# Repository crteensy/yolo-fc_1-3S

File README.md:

# Yolo FC, STM32F7, 1-3S
This FC has been test flown with a 3" toothpick, and it flew well.

- Main MCU: STM32F745
- IMU: ICM-20602
- Flash: 8MB
- Baro: BMP280
- OSD: '7456
- GNSS: Integrated GPS module (uBlox ZOE-M8Q) with u.Fl connector and experimental support for active antennas
- 4 ESCs:
  - EFM8BB21 / bluejay
  - Calculated current rating of 20A continuous 30A burst (depending on the airflow cooling situation)
- Current sensor: INA186 with 0m5 shunt - subjectively some of the best current measurements we have seen on any FC
- 4 multi purpose expansion connectors:
  - each with its own UART
  - shared I2C bus
  - 5V, 3V3 and GND
  - a multi-purpose pin for analog RSSI, Buzzer, LEDs, etc.
- One video expansion connector:
  - Camera in and VTx out
  - UART
  - 2 multi-purpose pins
  - switchable 5V (*)
- size: 30 x 25.2 mm

The expansion connectors can be used with very simple or more complex plug-ins for
- Rx of your choice
- Magnetometer
- Buzzer
- LED strip
- dual camera switching on the OSD connector
- even additional plugin ESCs for hexa- and octocopters are possible

*) The OSD connector has a 5V output that is only ON when USB is not plugged in. This protects your USB port from power hungry VTx'es that might overload the port. However, that feature can be disabled with a solder bridge.

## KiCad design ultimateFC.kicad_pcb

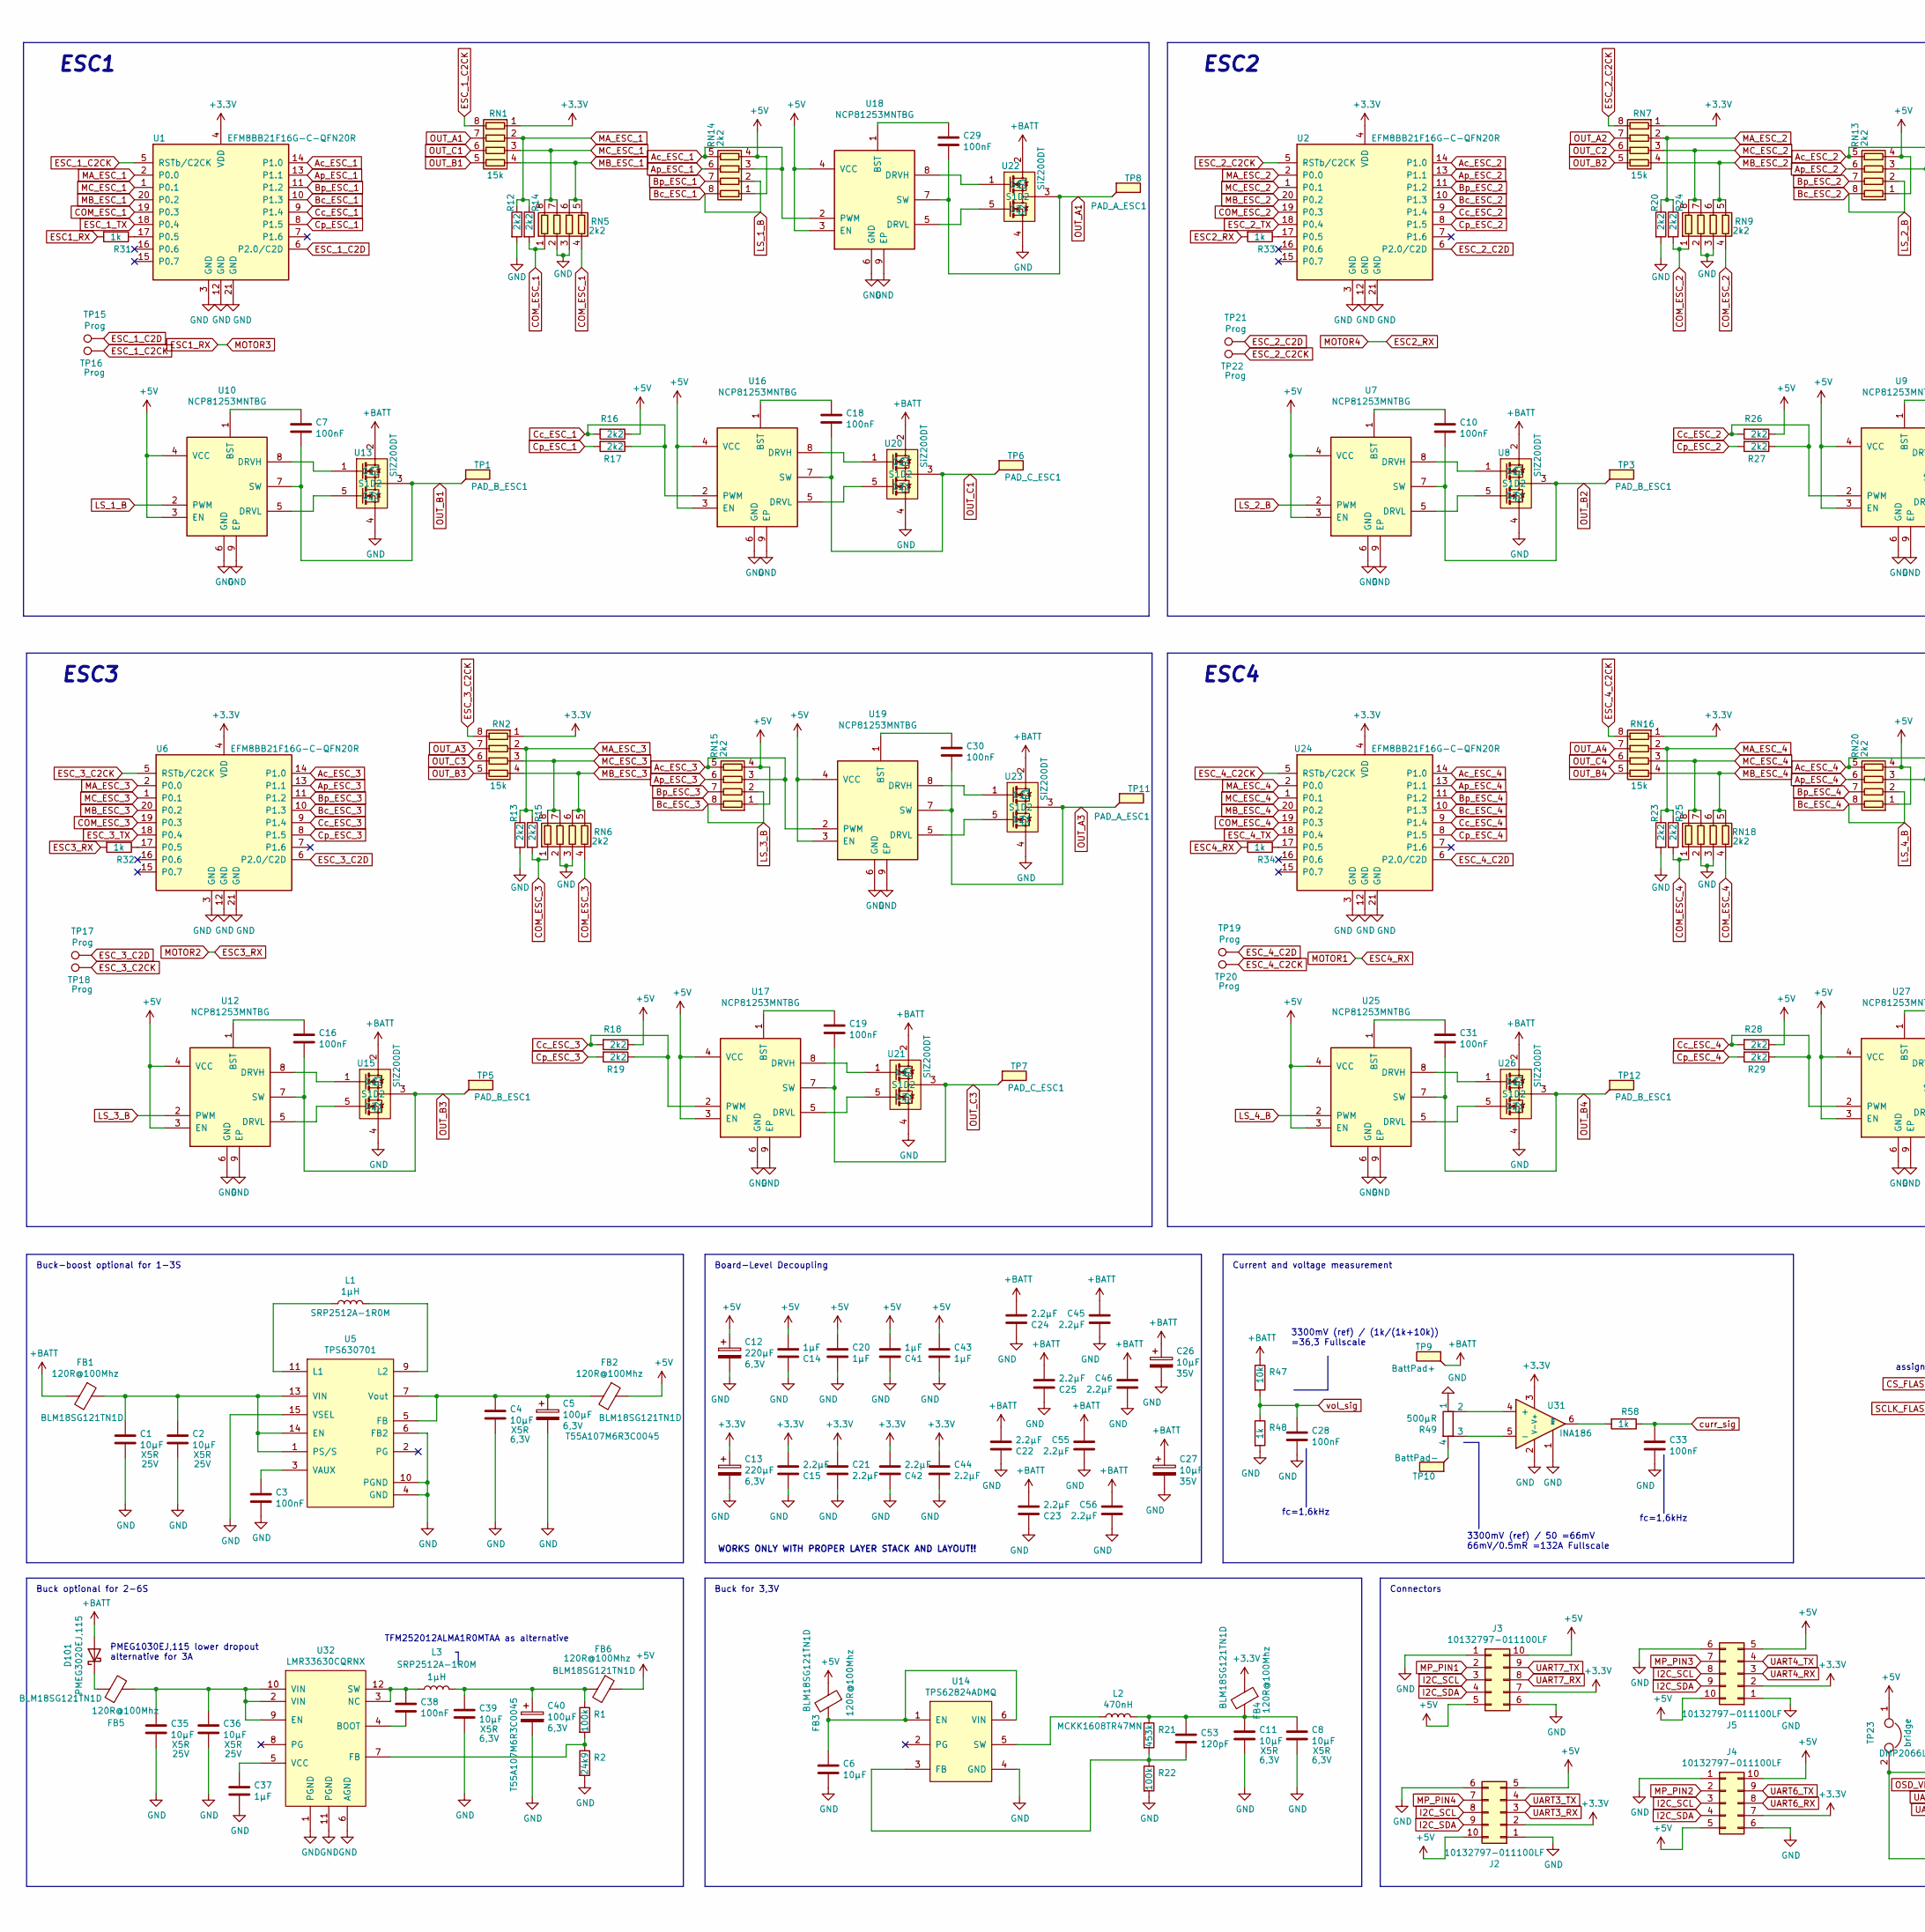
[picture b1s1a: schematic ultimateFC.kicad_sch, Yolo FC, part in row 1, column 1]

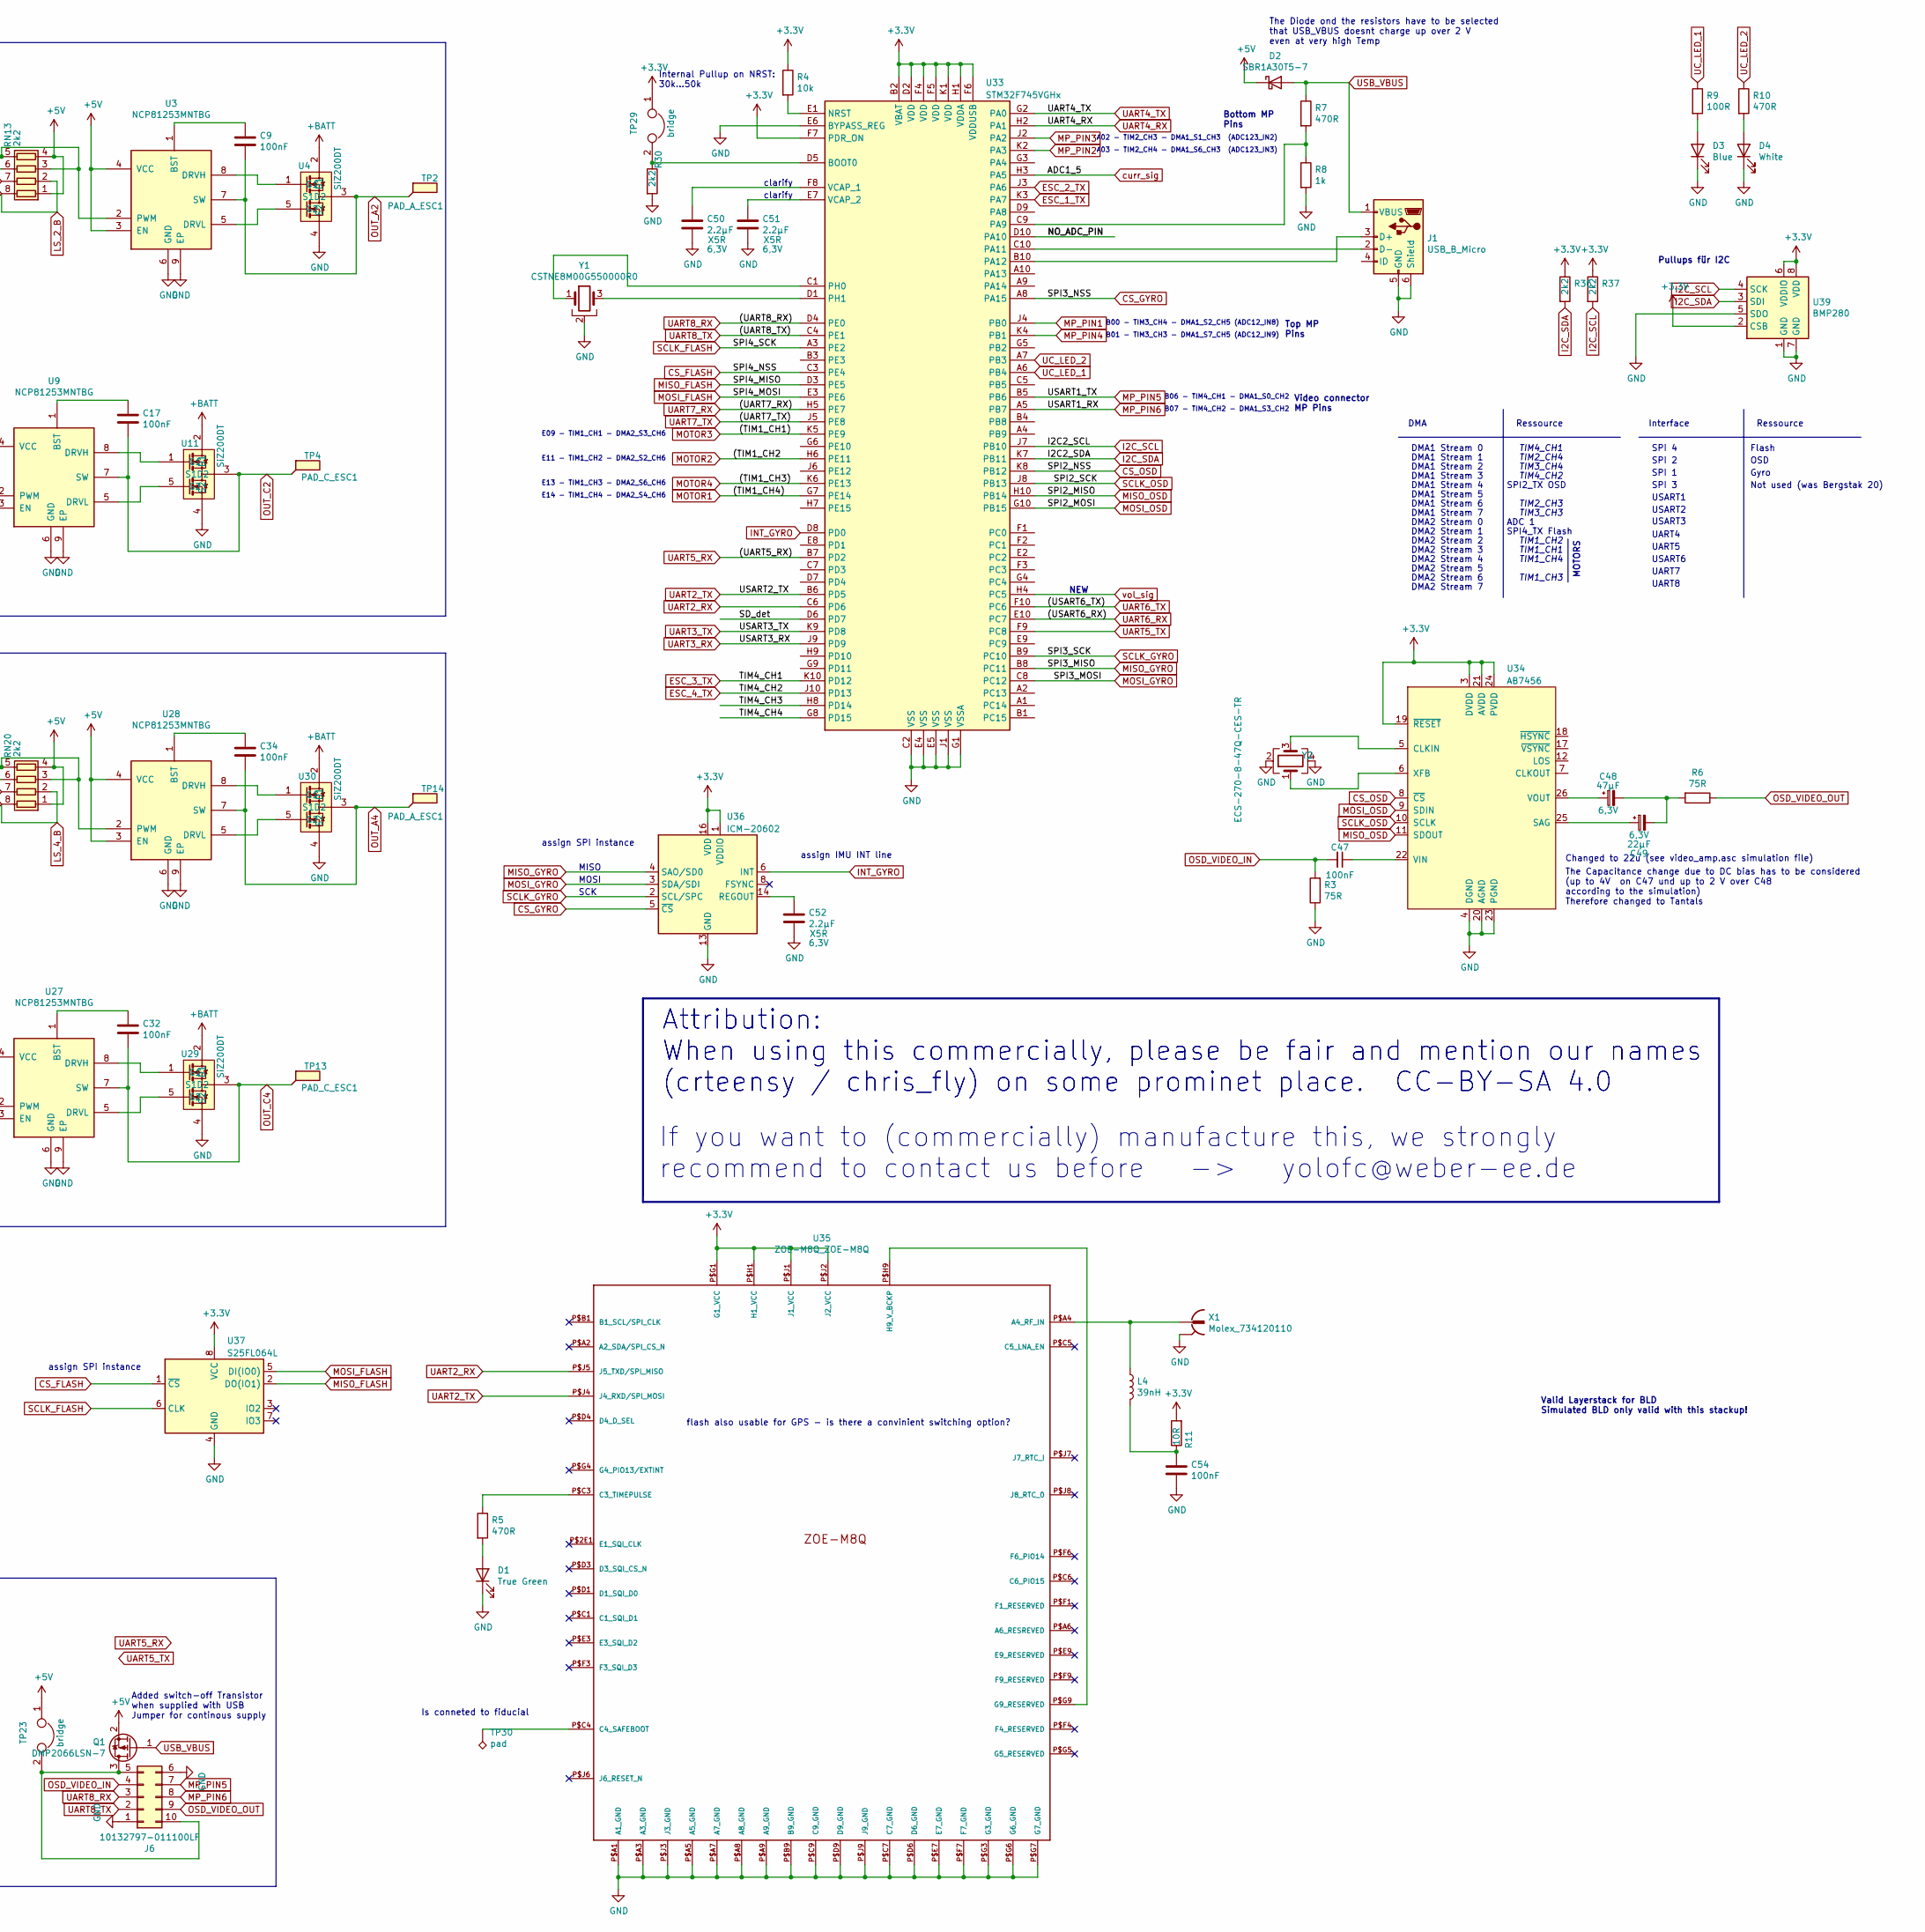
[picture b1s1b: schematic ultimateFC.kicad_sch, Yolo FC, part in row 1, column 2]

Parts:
C1, C2, C35, C36: 10µF; C_1206_3216Metric
C3, C28, C33, C38, C47, C54: 100nF; C_0201_0603Metric_mod
C4, C6, C8, C11, C39: 10µF; C_0603_1608Metric
C5, C40: 100µF; CP_EIA-3216-10_Kemet-I
C7, C9, C10, C16, C17, C18, C19, C29, C30, C31, C32, C34: 100nF; C_0402_1005Metric
C12, C13: 220µF; CP_EIA-3528-15_AVX-H
C14, C20, C41, C43: 1µF; C_AVX_Super_Low_ESL
C15, C21, C42, C44: 2.2µF; C_AVX_Super_Low_ESL
C22, C23, C24, C25, C45, C46, C55, C56: 2.2µF; C_0603_1608Metric
C26, C27: 10µF; CP_EIA-3216-18_Kemet-A
C37: 1µF; C_0402_1005Metric
C48: 47µF; C_0603_1608Metric
C49: 22µF; C_0603_1608Metric
C50, C51, C52: 2.2µF; C_0402_1005Metric
C53: 120pF; C_0201_0603Metric_mod
D1: True Green; LED_0201_0603Metric
D2: SBR1A30T5-7; D_SOD-523
D3: Blue; LED_0201_0603Metric
D4: White; LED_0201_0603Metric
D101: PMEG3020EJ,115; D_SOD-323
FB1, FB2, FB3, FB4, FB5, FB6: 120R@100Mhz; L_0603_1608Metric
J1: USB_B_Micro; USB_Micro-B_Molex_47346-0001
J2, J3, J4, J5, J6: 10132797-011100LF
L1, L3: 1µH; L_Wuerth_MAPI-2506
L2: 470nH; L_0603_1608Metric
L4: 39nH; L_0201_0603Metric
Q1: DMP2066LSN-7; SOT-323_SC-70
R1, R22: 100k; R_0201_0603Metric_mod
R2: 24k9; R_0201_0603Metric_mod
R3, R6: 75R; R_0402_1005Metric
R4: 10k; R_0201_0603Metric_mod
R5, R7, R10: 470R; R_0201_0603Metric_mod
R8, R31, R32, R33, R34, R48, R58: 1k; R_0201_0603Metric_mod
R9: 100R; R_0201_0603Metric_mod
R11: 10R; R_0201_0603Metric_mod
R12, R13, R14, R15, R16, R17, R18, R19, R20, R23, R24, R25, R26, R27, R28, R29, R30, R36, R37: 2k2; R_0201_0603Metric_mod
R21: 453k; R_0201_0603Metric_mod
R47: 10k; R_0402_1005Metric
R49: 500µR; R_Shunt_Vishay_WSKW0612
RN1, RN2, RN7, RN16: 15k; R_Array_Convex_4x0402
RN5, RN6, RN9, RN13, RN14, RN15, RN18, RN20: 2k2; EXB18V_0201x4
TP1, TP3, TP5, TP12: PAD_B_ESC1; esc_pad
TP2, TP8, TP11, TP14: PAD_A_ESC1; esc_pad
TP4, TP6, TP7, TP13: PAD_C_ESC1; esc_pad
TP9: BattPad+; batt_conn_oval
TP10: BattPad-; batt_conn_oval
TP15, TP16, TP17, TP18, TP19, TP20, TP21, TP22: Prog; programm_pad_esc
TP23, TP29: bridge; solderbridge_tiny
TP30: pad; TestPoint_Pad_1.0x1.0mm
U1, U2, U6, U24: EFM8BB21F16G-C-QFN20R; SiliconLabs_QFN-20-1EP_3x3mm_P0.5mm
U3, U7, U9, U10, U12, U16, U17, U18, U19, U25, U27, U28: NCP81253MNTBG; DFN-8-1EP_2x2mm_P0.5mm_EP0.9x1.3mm
U4, U8, U11, U13, U15, U20, U21, U22, U23, U26, U29, U30: SiZ200DT; PowerPAIR3.3x3.3
U5: TPS630701; TEXAS_15-VQFN-HR
U14: TPS62824ADMQ; VSON_HR6
U31: INA186; SOT-363_SC-70-6
U32: LMR33630CQRNX; Texas_RNX0012B
U33: STM32F745VGHx; TFBGA-100_8x8mm_Layout10x10_P0.8mm
U34: AB7456; TSSOP-28_4.4x9.7mm_P0.65mm
U35: ZOE-M8Q_ZOE-M8Q; ZOE-M8
U36: ICM-20602; LGA-16_3x3mm_P0.5mm_LayoutBorder3x5y
U37: S25FL064L; WSON-8_4x4mm_P0.8mm
U39: BMP280; Bosch_LGA-8_2x2.5mm_P0.65mm_ClockwisePinNumbering
X1: Molex_734120110
Y1: CSTNE8M00G550000R0; Resonator_SMD_muRata_CSTxExxV-3Pin_3.0x1.1mm
Y2: ECS-270-8-47Q-CES-TR; ECX-1247Q

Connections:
+3V3: C13.1, C15.2, C21.1, C42.2, C44.1, FB4.1, J2.2, J3.7, J4.7, J5.2, R4.1, R11.2, R36.1, R37.1, RN1.1 (R1.1), RN2.1 (R1.1), RN7.1 (R1.1), RN16.1 (R1.1), TP29.1, U1.4 (VDD), U2.4 (VDD), U6.4 (VDD), U24.4 (VDD), U31.3 (V+), U33.B2 (VBAT), U33.D2 (VDD), U33.F4 (VDD), U33.F5 (VDD), U33.F6 (VDDUSB), U33.F7 (PDR_ON), U33.H1 (VDDA), U33.K1 (VDD), U34.3 (DVDD), U34.19 (~RESET), U34.21 (AVDD), U34.24 (PVDD), U35.P$G1 (G1_VCC), U35.P$H1 (H1_VCC), U35.P$J1 (J1_VCC), U35.P$J2 (J2_VCC), U36.1 (VDDIO), U36.16 (VDD), U37.8 (VCC), U39.2 (CSB), U39.6 (VDDIO), U39.8 (VDD)
+5V: C12.1, C14.2, C20.1, C41.2, C43.1, D2.1 (K), FB2.1, FB3.1, FB6.1, J2.5, J2.10, J3.5, J3.10, J4.5, J4.10, J5.5, J5.10, Q1.2 (S), R16.1, R18.1, R26.1, R28.1, RN13.1 (R1.1), RN13.4 (R4.1), RN14.1 (R1.1), RN14.4 (R4.1), RN15.1 (R1.1), RN15.4 (R4.1), RN20.1 (R1.1), RN20.4 (R4.1), TP23.1, U3.3 (EN), U3.4 (VCC), U7.3 (EN), U7.4 (VCC), U9.3 (EN), U9.4 (VCC), U10.3 (EN), U10.4 (VCC), U12.3 (EN), U12.4 (VCC), U16.3 (EN), U16.4 (VCC), U17.3 (EN), U17.4 (VCC), U18.3 (EN), U18.4 (VCC), U19.3 (EN), U19.4 (VCC), U25.3 (EN), U25.4 (VCC), U27.3 (EN), U27.4 (VCC), U28.3 (EN), U28.4 (VCC)
+BATT: C22.2, C23.2, C24.2, C25.2, C26.1, C27.1, C45.1, C46.1, C55.1, C56.1, D101.2 (A), FB1.2, R47.1, TP9.1, U4.2 (D1), U8.2 (D1), U11.2 (D1), U13.2 (D1), U15.2 (D1), U20.2 (D1), U21.2 (D1), U22.2 (D1), U23.2 (D1), U26.2 (D1), U29.2 (D1), U30.2 (D1)
/NO_ADC_PIN: U33.D10 (PA10)
/SD_det: U33.D6 (PD7)
/TIM4_CH3: U33.H8 (PD14)
/TIM4_CH4: U33.G8 (PD15)
Ac_ESC_1: RN14.3 (R3.1), RN14.5 (R4.2), U1.14 (P1.0), U18.2 (PWM)
Ac_ESC_2: RN13.3 (R3.1), RN13.5 (R4.2), U2.14 (P1.0), U3.2 (PWM)
Ac_ESC_3: RN15.3 (R3.1), RN15.5 (R4.2), U6.14 (P1.0), U19.2 (PWM)
Ac_ESC_4: RN20.3 (R3.1), RN20.5 (R4.2), U24.14 (P1.0), U28.2 (PWM)
Ap_ESC_1: RN14.6 (R3.2), U1.13 (P1.1)
Ap_ESC_2: RN13.6 (R3.2), U2.13 (P1.1)
Ap_ESC_3: RN15.6 (R3.2), U6.13 (P1.1)
Ap_ESC_4: RN20.6 (R3.2), U24.13 (P1.1)
Bc_ESC_1: RN14.2 (R2.1), RN14.8 (R1.2), U1.10 (P1.3), U10.2 (PWM)
Bc_ESC_2: RN13.2 (R2.1), RN13.8 (R1.2), U2.10 (P1.3), U7.2 (PWM)
Bc_ESC_3: RN15.2 (R2.1), RN15.8 (R1.2), U6.10 (P1.3), U12.2 (PWM)
Bc_ESC_4: RN20.2 (R2.1), RN20.8 (R1.2), U24.10 (P1.3), U25.2 (PWM)
Bp_ESC_1: RN14.7 (R2.2), U1.11 (P1.2)
Bp_ESC_2: RN13.7 (R2.2), U2.11 (P1.2)
Bp_ESC_3: RN15.7 (R2.2), U6.11 (P1.2)
Bp_ESC_4: RN20.7 (R2.2), U24.11 (P1.2)
COM_ESC_1: R14.2, RN5.1 (R1.1), RN5.4 (R4.1), U1.19 (P0.3)
COM_ESC_2: R24.2, RN9.1 (R1.1), RN9.4 (R4.1), U2.19 (P0.3)
COM_ESC_3: R15.2, RN6.1 (R1.1), RN6.4 (R4.1), U6.19 (P0.3)
COM_ESC_4: R25.2, RN18.1 (R1.1), RN18.4 (R4.1), U24.19 (P0.3)
CS_FLASH: U33.C3 (PE4), U37.1 (~CS)
CS_GYRO: U33.A8 (PA15), U36.5 (~CS)
CS_OSD: U33.K8 (PB12), U34.8 (~CS)
Cc_ESC_1: R16.2, R17.1, U1.9 (P1.4), U16.2 (PWM)
Cc_ESC_2: R26.2, R27.1, U2.9 (P1.4), U9.2 (PWM)
Cc_ESC_3: R18.2, R19.1, U6.9 (P1.4), U17.2 (PWM)
Cc_ESC_4: R28.2, R29.1, U24.9 (P1.4), U27.2 (PWM)
Cp_ESC_1: R17.2, U1.8 (P1.5)
Cp_ESC_2: R27.2, U2.8 (P1.5)
Cp_ESC_3: R19.2, U6.8 (P1.5)
Cp_ESC_4: R29.2, U24.8 (P1.5)
ESC1_RX: R31.2, U33.K5 (PE9)
ESC2_RX: R33.2, U33.K6 (PE13)
ESC3_RX: R32.2, U33.H6 (PE11)
ESC4_RX: R34.2, U33.G7 (PE14)
ESC_1_C2CK: RN1.8 (R1.2), TP16.1, U1.5 (RSTb/C2CK)
ESC_1_C2D: TP15.1, U1.6 (P2.0/C2D)
ESC_1_TX: U1.18 (P0.4), U33.K3 (PA7)
ESC_2_C2CK: RN7.8 (R1.2), TP22.1, U2.5 (RSTb/C2CK)
ESC_2_C2D: TP21.1, U2.6 (P2.0/C2D)
ESC_2_TX: U2.18 (P0.4), U33.J3 (PA6)
ESC_3_C2CK: RN2.8 (R1.2), TP18.1, U6.5 (RSTb/C2CK)
ESC_3_C2D: TP17.1, U6.6 (P2.0/C2D)
ESC_3_TX: U6.18 (P0.4), U33.K10 (PD12)
ESC_4_C2CK: RN16.8 (R1.2), TP20.1, U24.5 (RSTb/C2CK)
ESC_4_C2D: TP19.1, U24.6 (P2.0/C2D)
ESC_4_TX: U24.18 (P0.4), U33.J10 (PD13)
GND: C1.2, C2.2, C3.2, C4.2, C5.2, C6.2, C8.2, C11.2, C12.2, C13.2, C14.1, C15.1, C20.2, C21.2, C22.1, C23.1, C24.1, C25.1, C26.2, C27.2, C28.2, C33.2, C35.2, C36.2, C37.2, C39.2, C40.2, C41.1, C42.1, C43.2, C44.2, C45.2, C46.2, C50.2, C51.2, C52.2, C54.2, C55.2, C56.2, D1.1 (K), D3.1 (K), D4.1 (K), J1.5 (GND), J1.6 (Shield), J2.1, J2.6, J3.1, J3.6, J4.1, J4.6, J5.1, J5.6, J6.1, J6.6, R2.2, R3.1, R8.2, R12.2, R13.2, R20.2, R22.2, R23.2, R30.2, R48.2, R49.1, RN5.2 (R2.1), RN5.3 (R3.1), RN6.2 (R2.1), RN6.3 (R3.1), RN9.2 (R2.1), RN9.3 (R3.1), RN18.2 (R2.1), RN18.3 (R3.1), U1.3 (GND), U1.12 (GND), U1.21 (GND), U2.3 (GND), U2.12 (GND), U2.21 (GND), U3.6 (GND), U3.9 (EP), U4.4 (S2), U5.4 (GND), U5.6 (FB2), U5.10 (PGND), U5.15 (VSEL), U6.3 (GND), U6.12 (GND), U6.21 (GND), U7.6 (GND), U7.9 (EP), U8.4 (S2), U9.6 (GND), U9.9 (EP), U10.6 (GND), U10.9 (EP), U11.4 (S2), U12.6 (GND), U12.9 (EP), U13.4 (S2), U14.4 (GND), U15.4 (S2), U16.6 (GND), U16.9 (EP), U17.6 (GND), U17.9 (EP), U18.6 (GND), U18.9 (EP), U19.6 (GND), U19.9 (EP), U20.4 (S2), U21.4 (S2), U22.4 (S2), U23.4 (S2), U24.3 (GND), U24.12 (GND), U24.21 (GND), U25.6 (GND), U25.9 (EP), U26.4 (S2), U27.6 (GND), U27.9 (EP), U28.6 (GND), U28.9 (EP), U29.4 (S2), U30.4 (S2), U31.1 (REF), U31.2 (V-), U32.1 (PGND), U32.6 (AGND), U32.11 (PGND), U33.C2 (VSS), U33.E4 (VSS), U33.E5 (VSS), U33.E6 (BYPASS_REG), U33.G1 (VSSA), U33.J1 (VSS), U34.4 (DGND), U34.20 (AGND), U34.23 (PGND), U35.P$A1 (A1_GND), U35.P$A3 (A3_GND), U35.P$A5 (A5_GND), U35.P$A7 (A7_GND), U35.P$A8 (A8_GND), U35.P$A9 (A9_GND), U35.P$B9 (B9_GND), U35.P$C7 (C7_GND), U35.P$C9 (C9_GND), U35.P$D6 (D6_GND), U35.P$D9 (D9_GND), U35.P$E7 (E7_GND), U35.P$F7 (F7_GND), U35.P$G3 (G3_GND), U35.P$G6 (G6_GND), U35.P$G7 (G7_GND), U35.P$J3 (J3_GND), U35.P$J9 (J9_GND), U36.9 (GND), U36.10 (GND), U36.11 (GND), U36.12 (GND), U36.13 (GND), U36.15 (GND), U37.4 (GND), U39.1 (GND), U39.5 (SDO), U39.7 (GND), X1.S@1 (2), X1.S@2 (2), X1.S@3 (2), Y1.2, Y2.2, Y2.4
I2C_SCL: J2.8, J3.3, J4.3, J5.8, R37.2, U33.J7 (PB10), U39.4 (SCK)
I2C_SDA: J2.9, J3.4, J4.4, J5.9, R36.2, U33.K7 (PB11), U39.3 (SDI)
INT_GYRO: U33.D8 (PD0), U36.6 (INT)
MA_ESC_1: R12.1, R14.1, RN1.2 (R2.1), U1.2 (P0.0)
MA_ESC_2: R20.1, R24.1, RN7.2 (R2.1), U2.2 (P0.0)
MA_ESC_3: R13.1, R15.1, RN2.2 (R2.1), U6.2 (P0.0)
MA_ESC_4: R23.1, R25.1, RN16.2 (R2.1), U24.2 (P0.0)
MB_ESC_1: RN1.4 (R4.1), RN5.5 (R4.2), RN5.6 (R3.2), U1.20 (P0.2)
MB_ESC_2: RN7.4 (R4.1), RN9.5 (R4.2), RN9.6 (R3.2), U2.20 (P0.2)
MB_ESC_3: RN2.4 (R4.1), RN6.5 (R4.2), RN6.6 (R3.2), U6.20 (P0.2)
MB_ESC_4: RN16.4 (R4.1), RN18.5 (R4.2), RN18.6 (R3.2), U24.20 (P0.2)
MC_ESC_1: RN1.3 (R3.1), RN5.7 (R2.2), RN5.8 (R1.2), U1.1 (P0.1)
MC_ESC_2: RN7.3 (R3.1), RN9.7 (R2.2), RN9.8 (R1.2), U2.1 (P0.1)
MC_ESC_3: RN2.3 (R3.1), RN6.7 (R2.2), RN6.8 (R1.2), U6.1 (P0.1)
MC_ESC_4: RN16.3 (R3.1), RN18.7 (R2.2), RN18.8 (R1.2), U24.1 (P0.1)
MISO_FLASH: U33.D3 (PE5), U37.2 (DO(IO1))
MISO_GYRO: U33.B8 (PC11), U36.4 (SAO/SD0)
MISO_OSD: U33.H10 (PB14), U34.11 (SDOUT)
MOSI_FLASH: U33.E3 (PE6), U37.5 (DI(IO0))
MOSI_GYRO: U33.C8 (PC12), U36.3 (SDA/SDI)
MOSI_OSD: U33.G10 (PB15), U34.9 (SDIN)
MP_PIN1: J3.2, U33.J4 (PB0)
MP_PIN2: J4.2, U33.K2 (PA3)
MP_PIN3: J5.7, U33.J2 (PA2)
MP_PIN4: J2.7, U33.K4 (PB1)
MP_PIN5: J6.7, U33.B5 (PB6)
MP_PIN6: J6.8, U33.A5 (PB7)
unnamed: C1.1, C2.1, FB1.1, U5.1 (PS/S), U5.13 (VIN), U5.14 (EN)
unnamed: C3.1, U5.3 (VAUX)
unnamed: C4.1, C5.1, FB2.2, U5.5 (FB), U5.7 (Vout)
unnamed: C6.1, FB3.2, U14.1 (EN), U14.6 (VIN)
unnamed: C7.1, U10.1 (BST)
unnamed: C9.1, U3.1 (BST)
unnamed: C10.1, U7.1 (BST)
unnamed: C8.1, C11.1, C53.1, FB4.2, L2.2, R21.1
unnamed: C16.1, U12.1 (BST)
unnamed: C17.1, U9.1 (BST)
unnamed: C18.1, U16.1 (BST)
unnamed: C19.1, U17.1 (BST)
unnamed: C29.1, U18.1 (BST)
unnamed: C30.1, U19.1 (BST)
unnamed: C31.1, U25.1 (BST)
unnamed: C32.1, U27.1 (BST)
unnamed: C34.1, U28.1 (BST)
unnamed: C35.1, C36.1, FB5.2, U32.2 (VIN), U32.9 (EN), U32.10 (VIN)
unnamed: C37.1, U32.5 (VCC)
unnamed: C38.1, L3.1, U32.3 (NC), U32.12 (SW)
unnamed: C38.2, U32.4 (BOOT)
unnamed: C39.1, C40.1, FB6.2, L3.2, R1.1
unnamed: C47.1, U34.22 (VIN)
unnamed: C48.1, U34.26 (VOUT)
unnamed: C48.2, C49.2, R6.2
unnamed: C49.1, U34.25 (SAG)
unnamed: C50.1, U33.F8 (VCAP_1)
unnamed: C51.1, U33.E7 (VCAP_2)
unnamed: C52.1, U36.14 (REGOUT)
unnamed: C53.2, R21.2, R22.1, U14.3 (FB)
unnamed: C54.1, L4.2, R11.1
unnamed: D1.2 (A), R5.2
unnamed: D3.2 (A), R9.2
unnamed: D4.2 (A), R10.2
unnamed: D101.1 (K), FB5.1
unnamed: J1.2 (D-), U33.C10 (PA11)
unnamed: J1.3 (D+), U33.B10 (PA12)
unnamed: J6.5, J6.10, Q1.3 (D), TP23.2
unnamed: L1.1, U5.11 (L1)
unnamed: L1.2, U5.9 (L2)
unnamed: L2.1, U14.5 (SW)
unnamed: L4.1, U35.P$A4 (A4_RF_IN), X1.1
unnamed: R1.2, R2.1, U32.7 (FB)
unnamed: R4.2, U33.E1 (NRST)
unnamed: R5.1, U35.P$C3 (C3_TIMEPULSE)
unnamed: R7.2, R8.1, U33.C9 (PA9)
unnamed: R30.1, TP29.2, U33.D5 (BOOT0)
unnamed: R31.1, U1.17 (P0.5)
unnamed: R32.1, U6.17 (P0.5)
unnamed: R33.1, U2.17 (P0.5)
unnamed: R34.1, U24.17 (P0.5)
unnamed: R49.2, U31.4 (+)
unnamed: R49.3, U31.5 (-)
unnamed: R49.4, TP10.1
unnamed: R58.2, U31.6
unnamed: TP30.1, U35.P$C4 (C4_SAFEBOOT)
unnamed: U3.5 (DRVL), U4.5 (G2)
unnamed: U3.8 (DRVH), U4.1 (G1)
unnamed: U7.5 (DRVL), U8.5 (G2)
unnamed: U7.8 (DRVH), U8.1 (G1)
unnamed: U10.5 (DRVL), U13.5 (G2)
unnamed: U10.8 (DRVH), U13.1 (G1)
unnamed: U9.8 (DRVH), U11.1 (G1)
unnamed: U9.5 (DRVL), U11.5 (G2)
unnamed: U12.5 (DRVL), U15.5 (G2)
unnamed: U12.8 (DRVH), U15.1 (G1)
unnamed: U16.5 (DRVL), U20.5 (G2)
unnamed: U16.8 (DRVH), U20.1 (G1)
unnamed: U17.5 (DRVL), U21.5 (G2)
unnamed: U17.8 (DRVH), U21.1 (G1)
unnamed: U18.5 (DRVL), U22.5 (G2)
unnamed: U18.8 (DRVH), U22.1 (G1)
unnamed: U19.5 (DRVL), U23.5 (G2)
unnamed: U19.8 (DRVH), U23.1 (G1)
unnamed: U25.5 (DRVL), U26.5 (G2)
unnamed: U25.8 (DRVH), U26.1 (G1)
unnamed: U27.5 (DRVL), U29.5 (G2)
unnamed: U27.8 (DRVH), U29.1 (G1)
unnamed: U28.5 (DRVL), U30.5 (G2)
unnamed: U28.8 (DRVH), U30.1 (G1)
unnamed: U33.C1 (PH0), Y1.1
unnamed: U33.D1 (PH1), Y1.3
unnamed: U34.5 (CLKIN), Y2.3
unnamed: U34.6 (XFB), Y2.1
unnamed: U35.P$G9 (G9_RESERVED), U35.P$H9 (H9_V_BCKP)
OSD_VIDEO_IN: C47.2, J6.4, R3.2
OSD_VIDEO_OUT: J6.9, R6.1
OUT_A1: C29.2, RN1.7 (R2.2), TP8.1, U18.7 (SW), U22.3 (S1D2)
OUT_A2: C9.2, RN7.7 (R2.2), TP2.1, U3.7 (SW), U4.3 (S1D2)
OUT_A3: C30.2, RN2.7 (R2.2), TP11.1, U19.7 (SW), U23.3 (S1D2)
OUT_A4: C34.2, RN16.7 (R2.2), TP14.1, U28.7 (SW), U30.3 (S1D2)
OUT_B1: C7.2, RN1.5 (R4.2), TP1.1, U10.7 (SW), U13.3 (S1D2)
OUT_B2: C10.2, RN7.5 (R4.2), TP3.1, U7.7 (SW), U8.3 (S1D2)
OUT_B3: C16.2, RN2.5 (R4.2), TP5.1, U12.7 (SW), U15.3 (S1D2)
OUT_B4: C31.2, RN16.5 (R4.2), TP12.1, U25.7 (SW), U26.3 (S1D2)
OUT_C1: C18.2, RN1.6 (R3.2), TP6.1, U16.7 (SW), U20.3 (S1D2)
OUT_C2: C17.2, RN7.6 (R3.2), TP4.1, U9.7 (SW), U11.3 (S1D2)
OUT_C3: C19.2, RN2.6 (R3.2), TP7.1, U17.7 (SW), U21.3 (S1D2)
OUT_C4: C32.2, RN16.6 (R3.2), TP13.1, U27.7 (SW), U29.3 (S1D2)
SCLK_FLASH: U33.A3 (PE2), U37.6 (CLK)
SCLK_GYRO: U33.B9 (PC10), U36.2 (SCL/SPC)
SCLK_OSD: U33.J8 (PB13), U34.10 (SCLK)
UART2_RX: U33.C6 (PD6), U35.P$J5 (J5_TXD/SPI_MISO)
UART2_TX: U33.B6 (PD5), U35.P$J4 (J4_RXD/SPI_MOSI)
UART3_RX: J2.3, U33.J9 (PD9)
UART3_TX: J2.4, U33.K9 (PD8)
UART4_RX: J5.3, U33.H2 (PA1)
UART4_TX: J5.4, U33.G2 (PA0)
UART5_RX: U33.B7 (PD2)
UART5_TX: U33.F9 (PC8)
UART6_RX: J4.8, U33.E10 (PC7)
UART6_TX: J4.9, U33.F10 (PC6)
UART7_RX: J3.8, U33.H5 (PE7)
UART7_TX: J3.9, U33.J5 (PE8)
UART8_RX: J6.3, U33.D4 (PE0)
UART8_TX: J6.2, U33.C4 (PE1)
UC_LED_1: R9.1, U33.A6 (PB4)
UC_LED_2: R10.1, U33.A7 (PB3)
USB_VBUS: D2.2 (A), J1.1 (VBUS), Q1.1 (G), R7.1
curr_sig: C33.1, R58.1, U33.H3 (PA5)
vol_sig: C28.1, R47.2, R48.1, U33.H4 (PC5)

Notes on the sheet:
E11 - TIM1_CH2 - DMA2_S2_CH6
E13 - TIM1_CH3 - DMA2_S6_CH6
Is conneted to fiducial
DMA1 Stream 6
TIM1_CH4
USART3
B07 - TIM4_CH2 - DMA1_S3_CH2
SPI 2
TFM252012ALMA1R0MTAA as alternative
3300mV (ref) / (1k/(1k+10k)) =36,3 Fullscale
Interface
A02 - TIM2_CH3 - DMA1_S1_CH3 (ADC123_IN2)
SPI 1
Attribution: When using this commercially, please be fair and mention our names (crteensy / chris_fly) on some prominet place. CC-BY-SA 4.0
Internal Pullup on NRST: 30k...50k
UART5
SPI2_TX OSD
SPI 4
A03 - TIM2_CH4 - DMA1_S6_CH3 (ADC123_IN3)
TIM4_CH1
DMA1 Stream 5
MOSI
OSD
SPI 3
Valid Layerstack for BLD Simulated BLD only valid with this stackup!
TIM2_CH3
SCK
DMA2 Stream 5
DMA2 Stream 0
UART8
Board-Level Decoupling
DMA1 Stream 7
3300mV (ref) / 50 =66mV 66mV/0.5mR =132A Fullscale
TIM1_CH1
B00 - TIM3_CH4 - DMA1_S2_CH5 (ADC12_IN8)
DMA
Connectors
B01 - TIM3_CH3 - DMA1_S7_CH5 (ADC12_IN9)
Buck-boost optional for 1-3S
USART2

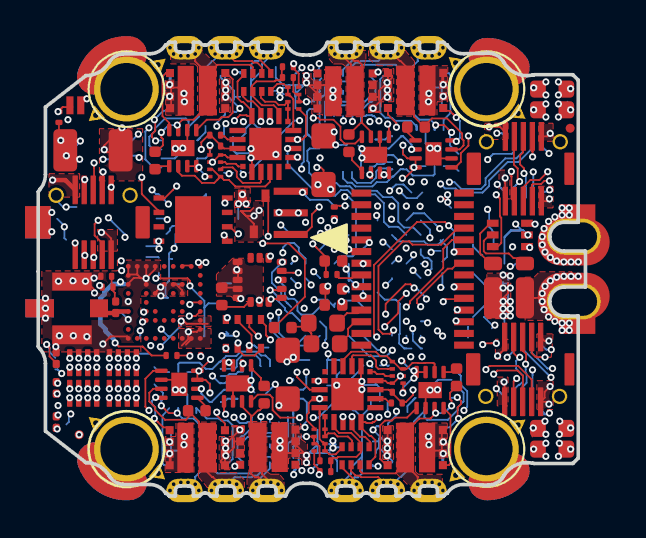
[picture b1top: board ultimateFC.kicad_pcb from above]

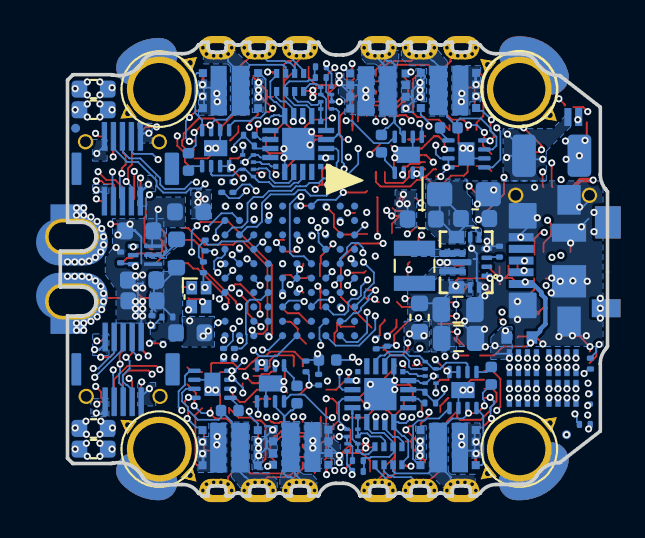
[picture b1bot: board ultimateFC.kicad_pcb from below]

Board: 8 copper layers, 30.4 x 25.2 mm, 182 parts (90 on the bottom side), 189 nets.

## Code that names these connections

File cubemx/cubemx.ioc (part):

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Mcu.Name=STM32F745V(E-G)Hx
Mcu.Package=TFBGA100
Mcu.UserName=STM32F745VGHx
PA0/WKUP.Mode=Asynchronous
PA0/WKUP.Signal=UART4_TX
PA1.Mode=Asynchronous
PA1.Signal=UART4_RX
PA11.Mode=Device_Only
PA11.Signal=USB_OTG_FS_DM
PA12.Mode=Device_Only
PA12.Signal=USB_OTG_FS_DP
PA15.Signal=SPI3_NSS
PA2.Signal=S_TIM2_CH3
PA3.Signal=S_TIM2_CH4
PA5.Signal=ADCx_IN5
PA6.Signal=S_TIM3_CH1
PA7.Signal=S_TIM3_CH2
PA9.Mode=Activate_VBUS
PA9.Signal=USB_OTG_FS_VBUS
PB0.Signal=S_TIM3_CH3
PB1.Signal=S_TIM3_CH4
PB10.Mode=I2C
PB10.Signal=I2C2_SCL
PB11.Mode=I2C
PB11.Signal=I2C2_SDA
PB12.Signal=SPI2_NSS
PB13.Mode=Full_Duplex_Master
PB13.Signal=SPI2_SCK
PB14.Mode=Full_Duplex_Master
PB14.Signal=SPI2_MISO
PB15.Mode=Full_Duplex_Master
PB15.Signal=SPI2_MOSI
PB3.Signal=GPIO_Output
PB4.Signal=GPIO_Output
PB6.Mode=Asynchronous
PB6.Signal=USART1_TX
PB7.Mode=Asynchronous
PB7.Signal=USART1_RX
PC10.Mode=Full_Duplex_Master
PC10.Signal=SPI3_SCK
PC11.Mode=Full_Duplex_Master
PC11.Signal=SPI3_MISO
PC12.Mode=Full_Duplex_Master
PC12.Signal=SPI3_MOSI
PC5.Signal=ADCx_IN15
PC6.Mode=Asynchronous
PC6.Signal=USART6_TX
PC7.Mode=Asynchronous
PC7.Signal=USART6_RX
PD0.Signal=GPIO_Input
PD12.Signal=S_TIM4_CH1
PD13.Signal=S_TIM4_CH2
PD2.Signal=UART5_RX
PD5.Mode=Asynchronous
PD5.Signal=USART2_TX
PD6.Mode=Asynchronous
PD6.Signal=USART2_RX
PD7.Signal=GPIO_Input
PD8.Mode=Asynchronous
PD8.Signal=USART3_TX
PD9.Mode=Asynchronous
PD9.Signal=USART3_RX
PE0.Mode=Asynchronous
PE0.Signal=UART8_RX
PE1.Mode=Asynchronous
PE1.Signal=UART8_TX
PE11.Signal=S_TIM1_CH2
PE13.Signal=S_TIM1_CH3
PE14.Signal=S_TIM1_CH4
PE2.Mode=Full_Duplex_Master
PE2.Signal=SPI4_SCK
PE4.Signal=SPI4_NSS
PE5.Mode=Full_Duplex_Master
PE5.Signal=SPI4_MISO
PE6.Mode=Full_Duplex_Master
PE6.Signal=SPI4_MOSI
PE7.Mode=Asynchronous
PE7.Signal=UART7_RX
PE8.Mode=Asynchronous
PE8.Signal=UART7_TX
PE9.Signal=S_TIM1_CH1
PH0/OSC_IN.Mode=HSE-External-Oscillator
PH0/OSC_IN.Signal=RCC_OSC_IN
PH1/OSC_OUT.Mode=HSE-External-Oscillator
PH1/OSC_OUT.Signal=RCC_OSC_OUT
RCC.HSE_VALUE=25000000
board=custom

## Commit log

2021-03-30 swap DCDC for 1-3S
2021-03-31 update layout
2021-03-31 update schematic
2021-03-31 remove references on silk screen
2021-05-24 updated 1-3s to newest board version
2021-05-24 update schematic pdf, add cubemx
2021-08-04 add assembly_output/*.pos
2021-08-24 fix fidu centers, update pos files
2021-09-17 fix DCDC footprint, remove some silkscreen
2022-03-27 update pcb to KiCad6 add assembly output gerbers
2023-05-02 cleanup before publish
2023-05-02 update readme, add license
2023-05-02 fix paste for 0201 components
